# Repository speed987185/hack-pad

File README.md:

# HACK-PAD
a hackpad made with blueprint guidance

#INTRODUCTION
I have made a hackpad with the guidance of hackclub, i made this project to be familiar with hardware, i added additional feature like oled display 

#HACKPAD
this respitory have CAD file which have top , bottom and complete hackpad step file.
pcb and shematic drawing are located at PCB section 

#FRIMWARE
i made a frimware using adrino as qmk didnt supported the microcontroller that i have used 

#FEATURES 
- have 3 button one do screen shot one open obs stdio and one open website of ysws hackclub.
- animation is played when nothing is going on in hack-pad a cool batman logo
- fake time it display fake time just to look cool you can modify the frimware and write anything you want to display

#shematic

#PCB

#CASE

hackclub is awesome..

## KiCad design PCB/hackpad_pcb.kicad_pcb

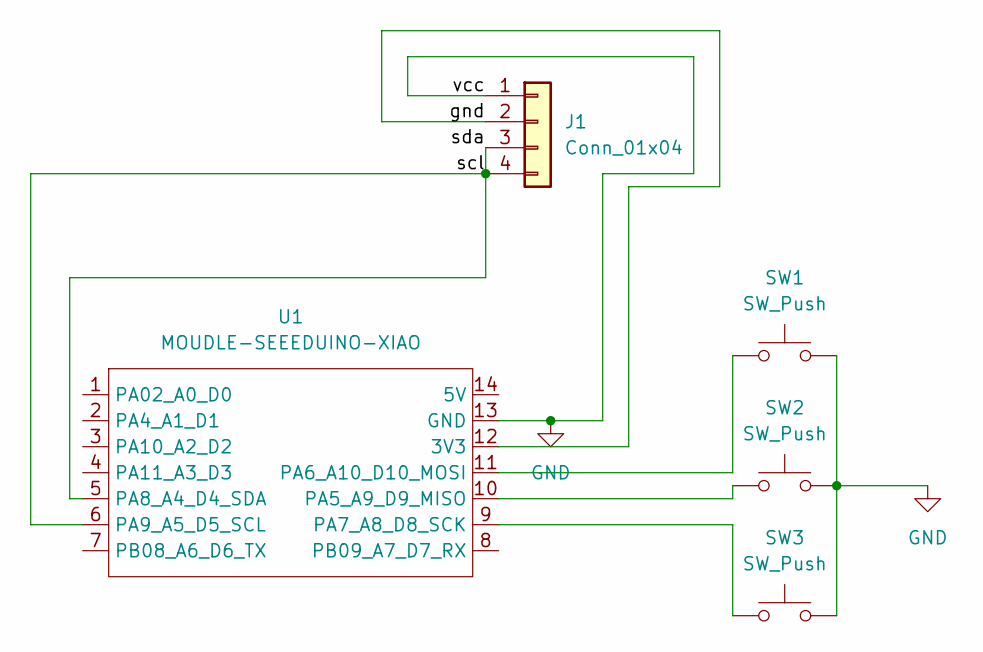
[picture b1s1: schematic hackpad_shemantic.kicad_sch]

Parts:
J1: Conn_01x04; PinHeader_1x04_P2.54mm_Vertical
SW1, SW2, SW3: SW_Push; SW_Cherry_MX_1.00u_PCB
U1: MOUDLE-SEEEDUINO-XIAO; XIAO-Generic-Hybrid-14P-2.54-21X17.8MM

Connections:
/gnd: J1.2, U1.12 (3V3)
/scl: J1.3, J1.4, U1.5 (PA8_A4_D4_SDA), U1.6 (PA9_A5_D5_SCL)
GND: J1.1, SW1.2, SW2.2, SW3.2, U1.13 (GND)
unnamed: SW2.1, U1.10 (PA5_A9_D9_MISO)
unnamed: SW1.1, U1.11 (PA6_A10_D10_MOSI)
unnamed: SW3.1, U1.9 (PA7_A8_D8_SCK)

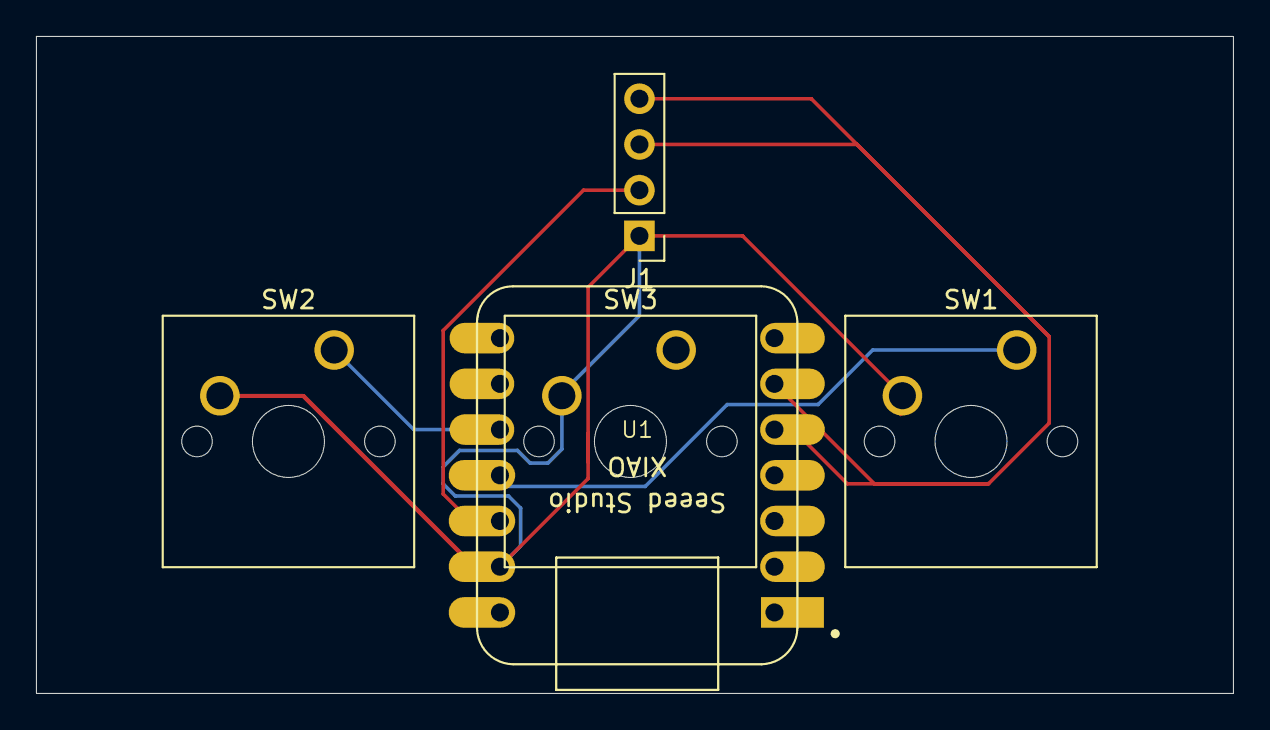
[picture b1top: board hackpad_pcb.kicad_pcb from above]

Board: 2 copper layers, 66.5 x 36.5 mm, 5 parts (0 on the bottom side), 6 nets.

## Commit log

2026-03-25 Rename pcb.kicad_pcb to PCB/pcb.kicad_pcb
2026-03-25 Rename shematic.kicad_sch to PCB/shematic.kicad_sch
2026-03-25 Rename abipad_default.hex to FRIMWARE/abipad_default.hex
2026-03-25 Rename hackpad.stl to CAD/hackpad.stl
2026-03-25 Rename hackpad_bottom.stl to CAD/hackpad_bottom.stl
2026-03-25 Rename hackpad_top.stl to CAD/hackpad_top.stl
2026-03-25 Update README with project introduction and details
    Added introduction and details about the hackpad project, including CAD files, PCB section, and firmware information.
2026-03-26 Rename Body46.step to CAD/hackpad_bottom.step
2026-03-26 Rename hackpad_top.step to CAD/hackpad_top.step
2026-03-26 Rename hackpad.step to CAD/hackpad.step
2026-03-26 Rename shematic.kicad_sch to PCB/hackpad_shemantic.kicad_sch
2026-03-26 Rename pcb_vvvv.kicad_pcb to CAD/hackpad_pcb.kicad_pcb
2026-03-26 Rename hackpad_pcb.kicad_pcb to hackpad_pcb.kicad_pcb
